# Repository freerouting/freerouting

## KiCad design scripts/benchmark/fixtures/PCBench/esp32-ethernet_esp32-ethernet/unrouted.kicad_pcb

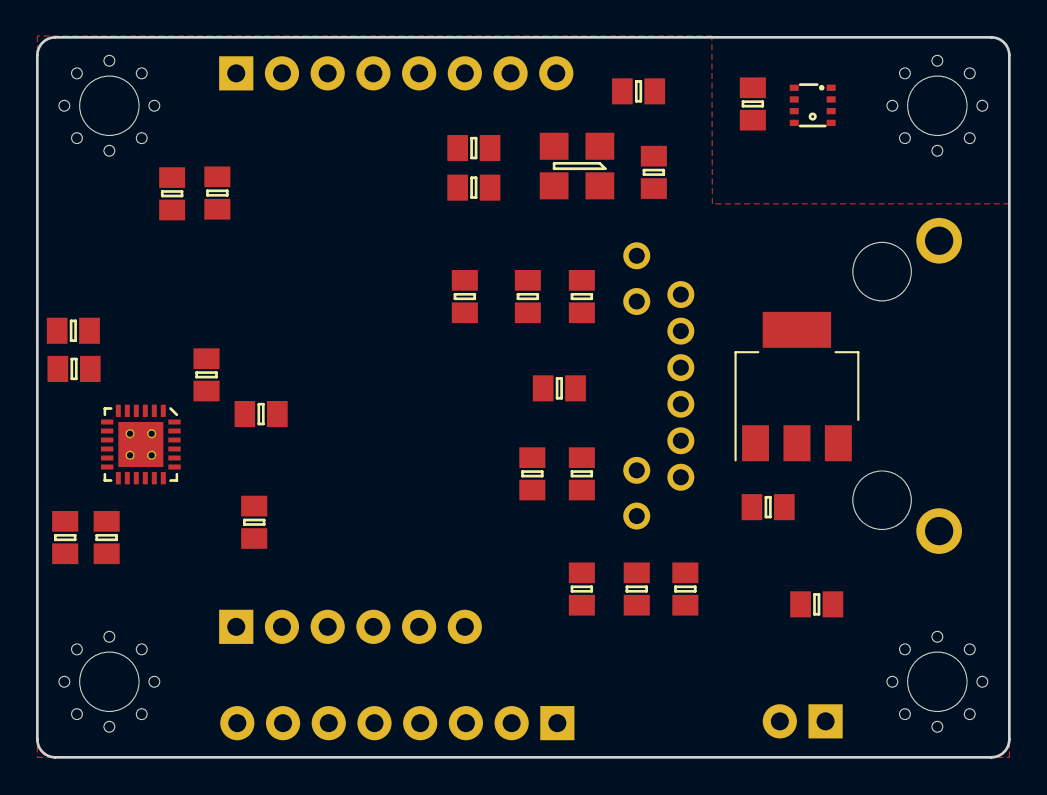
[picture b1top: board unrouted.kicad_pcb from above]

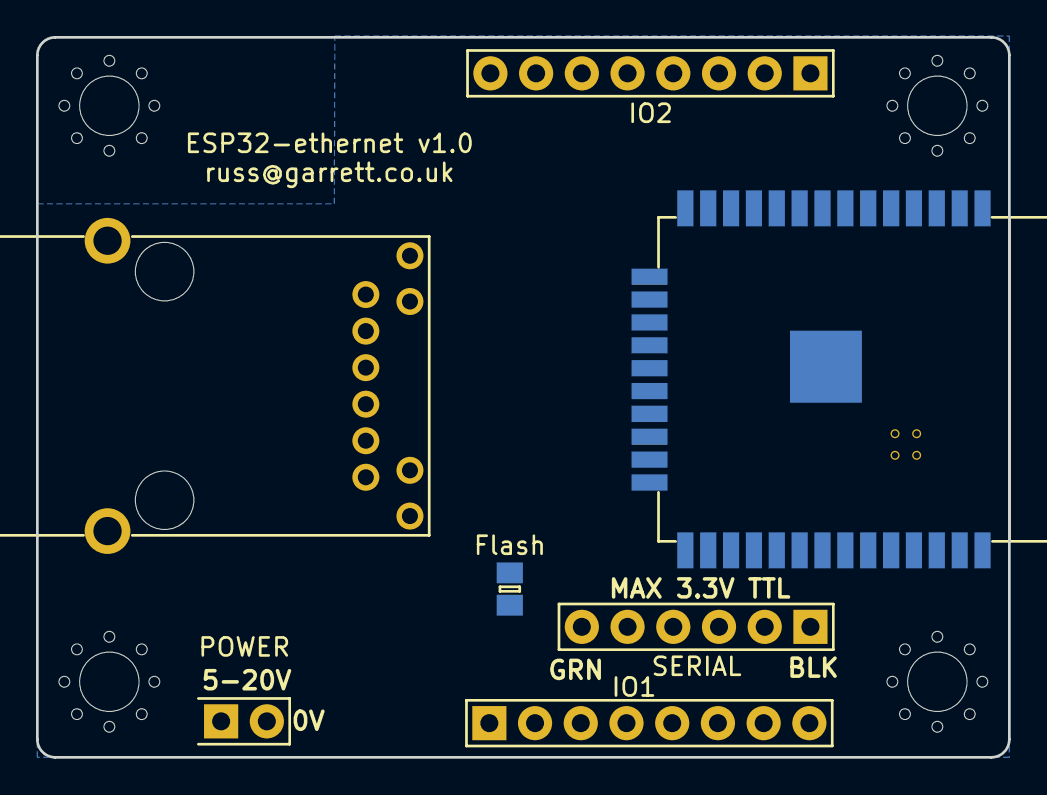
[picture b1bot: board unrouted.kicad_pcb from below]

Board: 2 copper layers, 54.0 x 40.0 mm, 36 parts (7 on the bottom side), 43 nets, no tracks yet.

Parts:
C1, C4, C5, C8, C9, C11: 0.1u; 0805
C2: 10u 50V; 0805
C3: 22u; 0805
C6: 10u; 0805
C7: 1u; 0805
C10: 470p; 0805
IC1: BME280
IC2: ESP-WROOM-32
IC3: NCP1117-3.3; SOT-223
IC4: LAN8720A; QFN-24-EP-MICROCHIP
IC5: RJMG16x; RJMG16X
J1: SERIAL; SIL-254P-06
J2: POWER; DIL-254P-02
J3: IO1; SIL-254P-08
J4: IO2; SIL-254P-08
JP1: Flash; 0805
L1: Bead; 0805
R1, R2: 4.7K; 0805
R3, R6: 4.7k; 0805
R4, R5: R; 0805
R7, R8, R10, R11: 49.9; 0805
R9: 12.1k 1%; 0805
R12, R13: 270; 0805
Y1: SG5032CAN 50MHz; SG5032CxN

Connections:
3v3: C1.1, C3.1, C6.1, C9.1, C11.2, IC1.2, IC1.6, IC1.8, IC2.2, IC3.2, IC3.4, IC4.9, IC5.10, J1.3, J3.1, L1.1, R1.1, R2.1, R3.1, Y1.4
/LAN_PHY/CLK: IC4.5, R5.2
/LAN_PHY/MDC: IC2.23, IC4.13
/LAN_PHY/MDIO: IC2.13, IC4.12
/LAN_PHY/RXD0: IC2.10, IC4.8
/LAN_PHY/RXD1: IC2.11, IC4.7
/LAN_PHY/RXER: IC2.16, IC4.10
/LAN_PHY/RX_DV: IC2.12, IC4.11
/LAN_PHY/TXD0: IC2.31, IC4.17
/LAN_PHY/TXD1: IC2.36, IC4.18
/LAN_PHY/TXEN: IC2.33, IC4.16
GND: C1.2, C2.2, C3.2, C4.2, C5.2, C6.2, C7.2, C8.2, C9.2, C10.2, C11.1, IC1.1, IC1.5, IC1.7, IC2.1, IC2.15, IC2.38, IC2.39, IC3.1, IC4.EP, IC5.S, J1.1, J2.2, J3.8, J4.8, JP1.1, R6.2, R9.1, R12.2, Y1.2
GPIO2: IC2.24, J3.2
GPIO4: IC2.26, J3.3
GPIO5: IC2.29, J3.4
GPIO12: IC2.14, J3.5
GPIO16: IC2.27, J3.6
GPIO18: IC2.30, J3.7
GPIO23: IC2.37, J4.1
GPIO32: IC2.8, J4.2
GPIO33: IC2.9, J4.3
GPIO36: IC2.4, J4.4
GPIO39: IC2.5, J4.5
I2C_SCL: IC1.4, IC2.6, J4.6, R1.2
I2C_SDA: IC1.3, IC2.7, J4.7, R2.2
LAN_VDD: C4.1, C5.1, C8.1, IC4.1, IC4.19, IC5.1, IC5.6, L1.2, R7.2, R8.2, R10.2, R11.2
LED1: IC4.3, IC5.8
LED2: IC4.2, R13.1
unnamed: C2.1, IC3.3, J2.1
unnamed: C7.1, C10.1, IC4.6
unnamed: IC2.3, J1.6
unnamed: IC2.25, JP1.2, R3.2, R4.2
unnamed: IC2.34, J1.4
unnamed: IC2.35, J1.5
unnamed: IC4.20, IC5.3, R8.1
unnamed: IC4.21, IC5.2, R7.1
unnamed: IC4.22, IC5.5, R11.1
unnamed: IC4.23, IC5.4, R10.1
unnamed: IC4.24, R9.2
unnamed: IC5.7, R12.1
unnamed: IC5.9, R13.2
PHY_CLK: R4.1, R5.1, Y1.3
PHY_CLK_EN: IC2.28, R6.1, Y1.1

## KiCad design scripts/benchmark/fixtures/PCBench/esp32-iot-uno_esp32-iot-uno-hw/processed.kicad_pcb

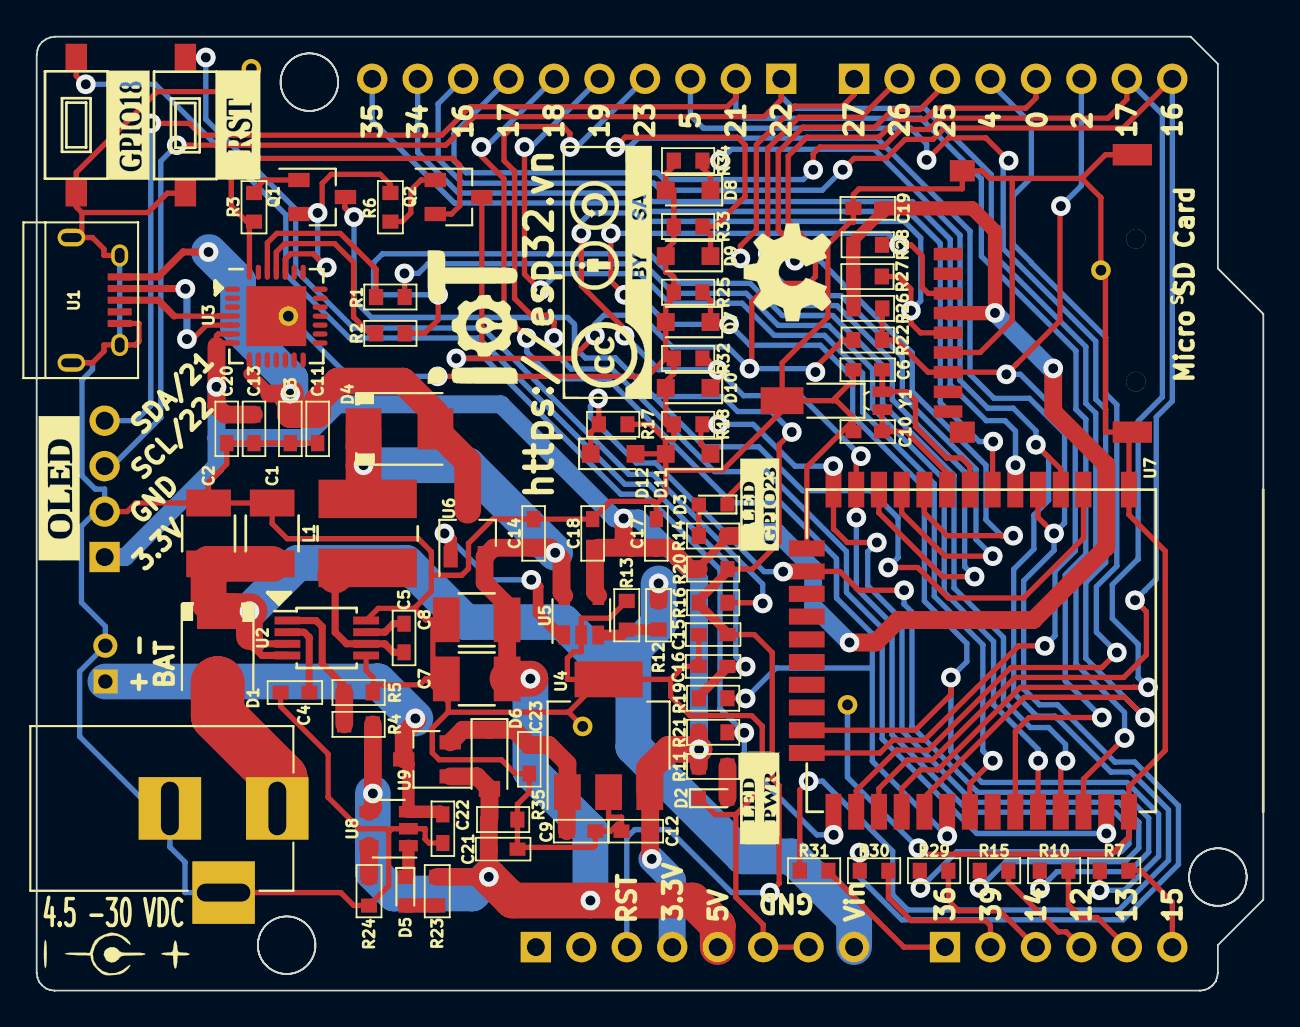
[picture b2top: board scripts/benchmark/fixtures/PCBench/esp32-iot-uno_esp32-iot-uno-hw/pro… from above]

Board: 2 copper layers, 68.5 x 53.3 mm, 91 parts (0 on the bottom side), 62 nets.

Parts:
BAT1: BAT; Pin_Header_Straight_2x01_Pitch2.00mm
C1, C2: 10uF/50V; C_1210
C3, C18, C20: 10uF; C_0603
C4, C9, C11, C12, C13, C23: 1uF; C_0603
C5, C14: 100nF; C_0603
C6, C10: 27pF/50V; C_0603
C7, C8: 10uF/25V; C_1210
C15, C16: 0.1uF/50V; C_0603
C17: 0.1uF; C_0603
C19: 10uF/25V; C_0603
C21, C22: 4,7uF; C_0603
CON1: BARREL_JACK
D1, D4: SS34; do214aa-g
D2: Led_PWR_G; LED_0603
D3: LED_IO23_W; LED_0603
D5: Led; LED_0603
D6: BAT60JFILM; D_SOD-123
D7, D8, D9, D10, D11, D12: D_Zener_3.3V; D_SOD-323_HandSoldering
L1: 22uH; Choke_SMD_Wuerth-WE-PD2-Typ-MS
P1, P2: GPIO; Pin_Header_Straight_1x08_Pitch2.54mm
P3: ADC; Pin_Header_Straight_1x06_Pitch2.54mm
P4: GPIO; Pin_Header_Straight_1x10_Pitch2.54mm
P5: OLED; Pin_Header_Straight_1x04_Pitch2.54mm
Q1, Q2: S8050_NPN_BEC; SOT-23_standar
R1, R2, R11, R14, R16, R19, R23: 470R; R_0603
R3, R6, R24: 10K; R_0603
R4: 52.5K; R_0603
R5, R12, R13, R20: 10k; R_0603
R7, R10, R15, R29, R30, R31: 33R/1%; R_0603
R17, R18, R25, R32, R33, R34: NC/1%; R_0603
R21, R22, R26, R27, R28: 10k/1%; R_0603
R35: 100K; R_0603
S1: SD_CARD; MicroSD_Push-Push-A
SW1: SW_EN; Tact_Switch_TS6X3.6
SW2: SW_IO18; Tact_Switch_TS6X3.6
U1: usb_mini_b; USB_Micro-B
U2: MCP16311-MNY; MSOP-8_3x3mm_Pitch0.65mm
U3: CP2102; QFN-28-1EP_5x5mm_Pitch0.5mm
U4: TC1264-3.3VDBTR; SOT-223-3Lead_TabPin2
U5: MCP601OT; SOT-23-5
U6: IRLM6402; SOT-23_standar
U7: ESP32; ESP-WROOM-32
U8: MCP73831/2; SOT-23-5
U9: DMP1045U; SOT-23_standar
Y1: 32.768KHz; Crystal_SMD_MicroCrystal_MS3V-T1R

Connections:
+3V3: C12.1, C13.1, C17.1, C18.1, C19.1, C20.1, P1.4, P5.1, R11.1, R14.1, R20.2, R21.2, R26.2, R27.2, R28.2, S1.4, U3.6, U3.7, U4.3, U5.4, U7.2
+5V: C7.1, C8.1, C14.1, C21.1, D4.1, D6.2, L1.2, P1.5, R4.1, R23.2, R35.2, U5.5, U6.2, U8.4, U9.1
+5VD: C9.1, C23.1, D6.1, U4.1, U9.2
A0/IO36: P3.1, R31.2
A1/IO39: P3.2, R30.2
A2/IO14: P3.3, R29.2
A3/IO12: P3.4, R15.2
A4/IO13: P3.5, R10.2
A5/IO15: P3.6, R7.2
ADC1_0/IO36: D8.1, R31.1, R34.2, U7.4
ADC1_3/IO39: D9.1, R30.1, R33.2, U7.5
ADC2_0/IO4: P2.4, U7.26
D+: U1.3, U3.4
D-: U1.2, U3.5
DTR: Q2.2, R3.1, U3.28
EN: C15.1, P1.3, Q1.3, R16.1, R20.1, U7.3
GND: BAT1.2, C1.2, C2.2, C3.2, C4.2, C6.2, C7.2, C8.2, C9.2, C10.2, C11.2, C12.2, C13.2, C14.2, C15.2, C16.2, C17.2, C18.2, C19.2, C20.2, C21.2, C22.2, C23.2, CON1.2, CON1.3, D2.1, D7.2, D8.2, D9.2, D10.2, D11.2, D12.2, P1.6, P1.7, P5.2, R5.2, R13.1, R17.1, R18.1, R24.1, R25.1, R32.1, R33.1, R34.1, R35.1, S1.6, S1.11, S1.12, SW1.2, SW2.1, U1.5, U1.6, U2.5, U2.8, U4.2, U5.2, U7.1, U7.15, U7.38, U8.2, Y1.3
IO0: P2.5, Q2.3, R21.1, R22.1, U7.25
IO2/DATA0: P2.6, R22.2, R26.1, S1.7, U7.24
IO5: P4.3, U7.29
IO12: D11.1, R15.1, R18.2, U7.14
IO13: D12.1, R10.1, R17.2, U7.16
IO14/CLK: D10.1, R27.1, R29.1, R32.2, S1.5, U7.13
IO15/CMD: D7.1, R7.1, R25.2, R28.1, S1.3, U7.23
IO16/U2RXD: P2.8, P4.8, U7.27
IO17/U2TXD: P2.7, P4.7, U7.28
IO18: P4.6, R19.1, U7.30
IO19: P4.5, U7.31
IO21/SDA: P4.2, P5.4, U7.33
IO22/SCL: P4.1, P5.3, U7.36
IO23: D3.1, P4.4, U7.37
IO25: P2.3, U7.10
IO26: P2.2, U7.11
IO27: P2.1, U7.12
IO32: C6.1, U7.8, Y1.1
IO33: C10.1, U7.9, Y1.2
IO34: P4.9, U7.6
IO35: P4.10, U7.7
unnamed: BAT1.1, C22.1, U8.3, U9.3
unnamed: C4.1, U2.2
unnamed: C5.1, U2.7
unnamed: C5.2, L1.1, U2.6
unnamed: C16.1, R19.2, SW2.2
unnamed: CON1.1, D1.2
unnamed: D2.2, R11.2
unnamed: D3.2, R14.2
unnamed: D5.1, U8.1
unnamed: D5.2, R23.1
unnamed: Q1.1, R3.2
unnamed: Q2.1, R6.2
unnamed: R4.2, R5.1, U2.1
unnamed: R12.1, R13.2, U5.3
unnamed: R16.2, SW1.1
unnamed: R24.2, U8.5
unnamed: U5.1, U6.1
RTS: Q1.2, R6.1, U3.24
RXD: R1.1, U7.34
RXD_CP2102: R2.2, U3.25
TXD: R2.1, U7.35
TXD_CP2102: R1.2, U3.26
VCC: C3.1, C11.1, D4.2, U1.1, U3.8, U6.3
Vin: C1.1, C2.1, D1.1, P1.8, R12.2, U2.3, U2.4

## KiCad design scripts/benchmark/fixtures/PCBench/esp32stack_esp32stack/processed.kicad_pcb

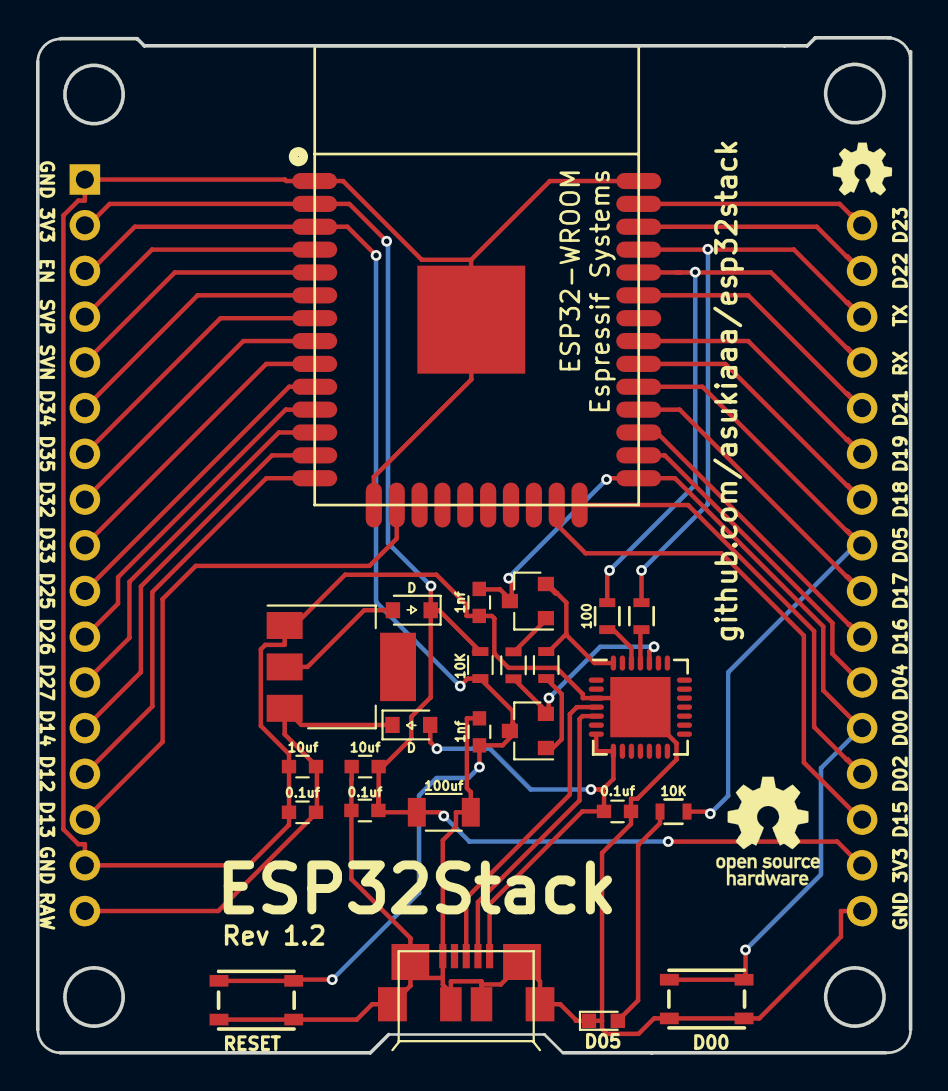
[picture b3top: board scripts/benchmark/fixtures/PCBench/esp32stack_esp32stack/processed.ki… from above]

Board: 2 copper layers, 48.5 x 56.4 mm, 27 parts (0 on the bottom side), 41 nets.

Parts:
C1, C2: 1nf; C_0603
C3, C4: 10uf; C_0603
C5, C6, C7: 0.1uf; C_0603
C8: 100uf; C_1206
D1, D2: D; D_0805
D3: D05; LED_0603
J1: CONN_01X17; Pin_Header_Straight_1x17_Pitch2.54mm
J2: CONN_01X16; Pin_Header_Straight_1x16_Pitch2.54mm
P1: USB_OTG; USB_MICRO_B-HIROSE-ZX62R-B-5P
Q1, Q2: MMBT3904; SOT-23
R1, R2, R3, R4: 10K; R_0603
R5, R6: 100; R_0603
SW1, SW2: SWITCH_SPST; SKRPACE010
U1: ESP32-WROOM
U2: NCP1117ST33T3G; SOT-223
U3: CP2102; QFN-28-1EP_5x5mm_Pitch0.5mm

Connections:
+3V3: C3.1, C7.1, C8.1, D2.1, J1.2, J2.15, R3.2, U1.2
+5V: C6.1, D1.2, P1.1, U3.7, U3.8
D+: P1.3, U3.4
D-: P1.2, U3.5
DTR: Q2.2, R1.1, U3.28
EN: C1.1, J1.3, Q1.3, R3.1, SW2.1, U1.3
GND: C1.2, C2.2, C3.2, C4.2, C5.2, C6.2, C7.2, C8.2, D3.1, J1.1, J1.16, J2.16, P1.5, P1.6, SW1.2, SW2.2, U1.1, U1.15, U1.38, U1.39, U2.1, U3.3, U3.29
IO0(boot): C2.1, J2.12, Q2.3, SW1.1, U1.25
IO2: J2.13, U1.24
IO4: J2.11, U1.26
IO5: J2.8, R4.1, U1.29
IO12: J1.14, U1.14
IO13: J1.15, U1.16
IO14: J1.13, U1.13
IO15: J2.14, U1.23
IO16: J2.10, U1.27
IO17: J2.9, U1.28
IO18: J2.7, U1.30
IO19: J2.6, U1.31
IO21: J2.5, U1.33
IO22: J2.2, U1.36
IO23: J2.1, U1.37
IO25: J1.10, U1.10
IO26: J1.11, U1.11
IO27: J1.12, U1.12
IO32: J1.8, U1.8
IO33: J1.9, U1.9
IO34: J1.6, U1.6
IO35: J1.7, U1.7
unnamed: D2.2, U2.2
unnamed: D3.2, R4.2
unnamed: Q1.1, R1.2
unnamed: Q2.1, R2.2
unnamed: R5.2, U3.25
unnamed: R6.2, U3.26
RTS: Q1.2, R2.1, U3.24
RXDtoTXD0: J2.3, R5.1, U1.35
SVN: J1.5, U1.5
SVP: J1.4, U1.4
TXDtoRXD0: J2.4, R6.1, U1.34
VCC: C4.1, C5.1, D1.1, J1.17, U2.3

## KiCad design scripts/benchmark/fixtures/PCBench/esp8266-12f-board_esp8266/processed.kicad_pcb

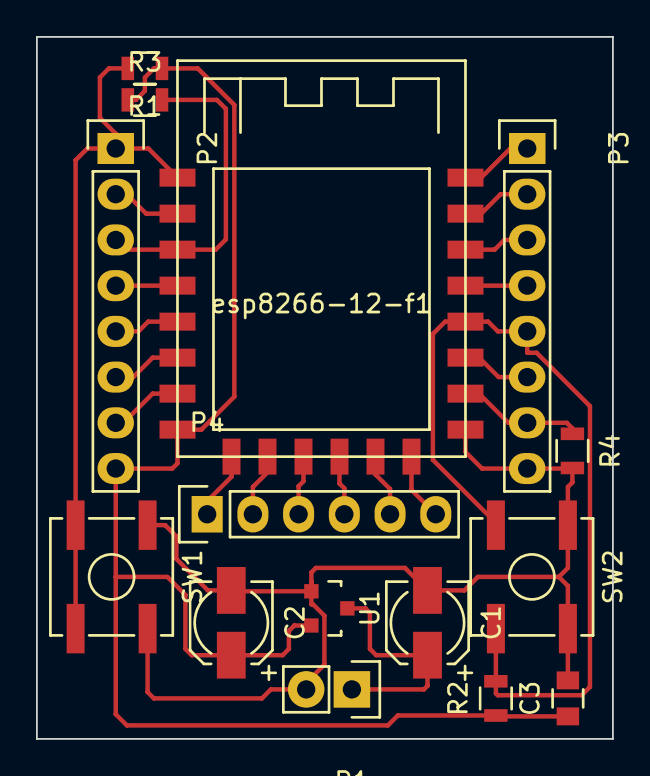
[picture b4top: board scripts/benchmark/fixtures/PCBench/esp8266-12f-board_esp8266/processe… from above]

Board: 2 copper layers, 32.0 x 39.0 mm, 15 parts (0 on the bottom side), 23 nets.

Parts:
C1, C2: 10μf; c_elec_4x5.8
C3: 100μ; C_0805
P1: VIN; Socket_Strip_Straight_1x02
P2, P3: CONN_01X08; Socket_Strip_Straight_1x08
P4: CONN_01X06; Socket_Strip_Straight_1x06
R1, R2, R3, R4: 10K; R_0805
SW1, SW2: SW_PUSH; SW_SPST_B3SL-1002P
U1: APE8865N-33-HF-3; SOT-23
esp8266-12-f1: esp8266-12f

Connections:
/ADC: P2.2, esp8266-12-f1.2
/CS0: P4.1, esp8266-12-f1.9
/EN: P2.3, R3.2, esp8266-12-f1.3
/GPIO0: P3.5, R2.2, SW2.2, esp8266-12-f1.18
/GPIO2: P3.6, esp8266-12-f1.17
/GPIO4: P3.4, esp8266-12-f1.19
/GPIO5: P3.3, esp8266-12-f1.20
/GPIO9: P4.3, esp8266-12-f1.11
/GPIO10: P4.4, esp8266-12-f1.12
/GPIO12: P2.6, esp8266-12-f1.6
/GPIO13: P2.7, esp8266-12-f1.7
/GPIO14: P2.5, esp8266-12-f1.5
/GPIO15: P3.7, R4.1, esp8266-12-f1.16
/GPIO16: P2.4, esp8266-12-f1.4
/MISO: P4.2, esp8266-12-f1.10
/MOSI: P4.5, esp8266-12-f1.13
/RST: P2.1, R1.2, SW1.2, esp8266-12-f1.1
/RXD: P3.2, esp8266-12-f1.21
/SCLK: P4.6, esp8266-12-f1.14
/TXD: P3.1, esp8266-12-f1.22
GND: C1.2, C2.2, C3.2, P1.2, P3.8, R4.2, SW1.1, SW2.1, U1.1, esp8266-12-f1.15
unnamed: C1.1, P1.1, U1.3
VCC: C2.1, C3.1, P2.8, R1.1, R2.1, R3.1, U1.2, esp8266-12-f1.8
